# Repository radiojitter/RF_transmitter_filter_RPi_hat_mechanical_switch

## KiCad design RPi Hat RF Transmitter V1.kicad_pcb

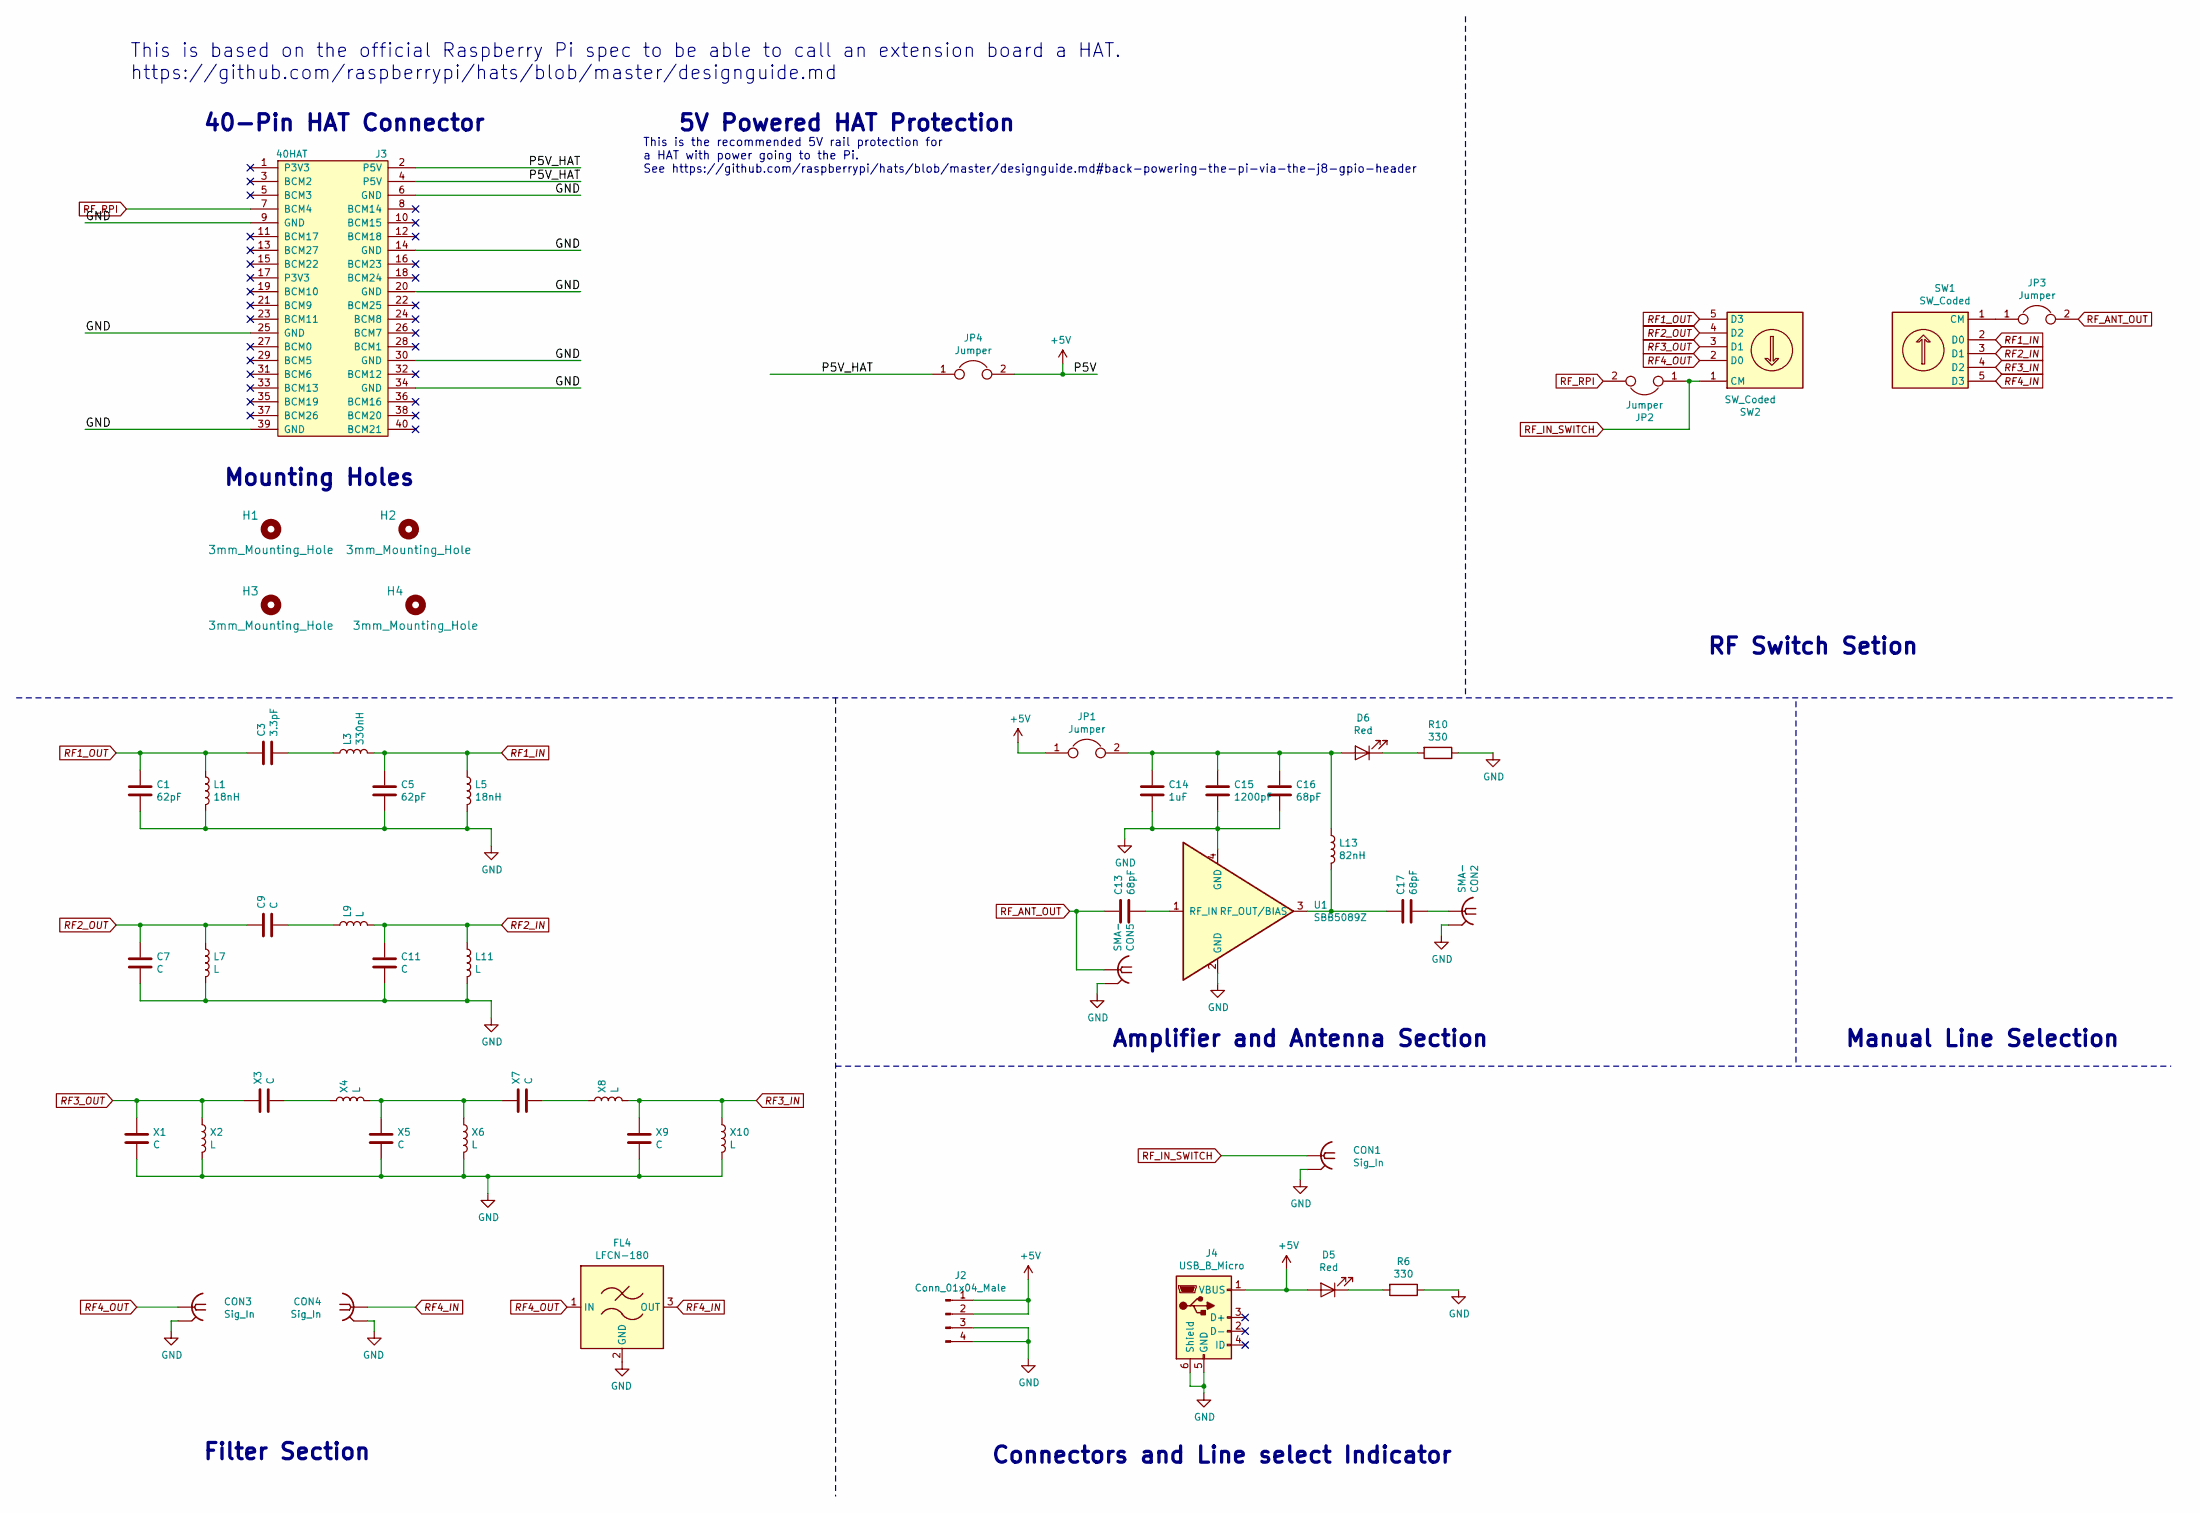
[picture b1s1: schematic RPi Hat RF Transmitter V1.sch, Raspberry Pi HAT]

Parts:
C1, C5: 62pF; C_0805_2012Metric_Pad1.15x1.40mm_HandSolder
C3: 3.3pF; C_0805_2012Metric_Pad1.15x1.40mm_HandSolder
C7, C9, C11: C; C_0805_2012Metric_Pad1.15x1.40mm_HandSolder
C13, C16, C17: 68pF; C_0805_2012Metric_Pad1.15x1.40mm_HandSolder
C14: 1uF; C_0805_2012Metric_Pad1.15x1.40mm_HandSolder
C15: 1200pF; C_0805_2012Metric_Pad1.15x1.40mm_HandSolder
CON1, CON3, CON4: Sig_In; SMA_Amphenol_132291-12_Vertical
CON2, CON5: SMA-; SMA_Amphenol_132291-12_Vertical
D5, D6: Red; LED_0805_2012Metric_Pad1.15x1.40mm_HandSolder
FL4: LFCN-180; Filter_Mini-Circuits_FV1206
H1, H2, H3, H4: 3mm_Mounting_Hole; NPTH_3mm_ID
J2: Conn_01x04_Male; PinHeader_1x04_P2.54mm_Vertical
J3: 40HAT; PinSocket_2x20_P2.54mm_Vertical
J4: USB_B_Micro; USB_Micro-B_Molex-105017-0001
JP1, JP2, JP3, JP4: Jumper; PinHeader_1x02_P2.54mm_Vertical
L1, L5: 18nH; L_0805_2012Metric_Pad1.15x1.40mm_HandSolder
L3: 330nH; L_0805_2012Metric_Pad1.15x1.40mm_HandSolder
L7, L9, L11: L; L_0805_2012Metric_Pad1.15x1.40mm_HandSolder
L13: 82nH; L_0805_2012Metric_Pad1.15x1.40mm_HandSolder
R6, R10: 330; R_0805_2012Metric_Pad1.15x1.40mm_HandSolder
SW1, SW2: SW_Coded; 1x4_switch
U1: SBB5089Z
X1, X3, X5, X7, X9: C; C_0805_2012Metric_Pad1.15x1.40mm_HandSolder
X2, X4, X6, X8, X10: L; L_0805_2012Metric_Pad1.15x1.40mm_HandSolder

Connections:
+5V: D5.2 (A), J2.1, J2.2, J4.1 (VBUS), JP1.1, JP4.2
/P5V_HAT: J3.2 (P5V), J3.4 (P5V), JP4.1
GND: C1.2, C5.2, C7.2, C11.2, C14.2, C15.2, C16.2, CON1.2, CON2.2, CON3.2, CON4.2, CON5.2, FL4.2 (GND), FL4.4 (GND), J2.3, J2.4, J3.6 (GND), J3.9 (GND), J3.14 (GND), J3.20 (GND), J3.25 (GND), J3.30 (GND), J3.34 (GND), J3.39 (GND), J4.5 (GND), J4.6 (Shield), L1.2, L5.2, L7.2, L11.2, R6.1, R10.1, U1.2 (GND), U1.4 (GND), X1.2, X2.2, X5.2, X6.2, X9.2, X10.2
unnamed: C3.2, L3.1
unnamed: C9.2, L9.1
unnamed: C13.2, U1.1 (RF_IN)
unnamed: C14.1, C15.1, C16.1, D6.2 (A), JP1.2, L13.1
unnamed: C17.1, L13.2, U1.3 (RF_OUT/BIAS)
unnamed: C17.2, CON2.1
unnamed: D5.1 (K), R6.2
unnamed: D6.1 (K), R10.2
unnamed: JP3.1, SW1.1 (CM)
unnamed: X3.2, X4.1
unnamed: X4.2, X5.1, X6.1, X7.1
unnamed: X7.2, X8.1
RF1_IN: C5.1, L3.2, L5.1, SW1.2 (D0)
RF1_OUT: C1.1, C3.1, L1.1, SW2.5 (D3)
RF2_IN: C11.1, L9.2, L11.1, SW1.3 (D1)
RF2_OUT: C7.1, C9.1, L7.1, SW2.4 (D2)
RF3_IN: SW1.4 (D2), X8.2, X9.1, X10.1
RF3_OUT: SW2.3 (D1), X1.1, X2.1, X3.1
RF4_IN: CON4.1, FL4.3 (OUT), SW1.5 (D3)
RF4_OUT: CON3.1, FL4.1 (IN), SW2.2 (D0)
RF_ANT_OUT: C13.1, CON5.1, JP3.2
RF_IN_SWITCH: CON1.1, JP2.1, SW2.1 (CM)
RF_RPI: J3.7 (BCM4), JP2.2

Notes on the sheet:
5V Powered HAT Protection
This is the recommended 5V rail protection for a HAT with power going to the Pi. See https://github.com/raspberrypi/hats/blob/master/designguide.md#back-powering-the-pi-via-the-j8-gpio-header
Mounting Holes
40-Pin HAT Connector
This is based on the official Raspberry Pi spec to be able to call an extension board a HAT. https://github.com/raspberrypi/hats/blob/master/designguide.md
Filter Section
RF Switch Setion
Amplifier and Antenna Section
Connectors and Line select Indicator
Manual Line Selection

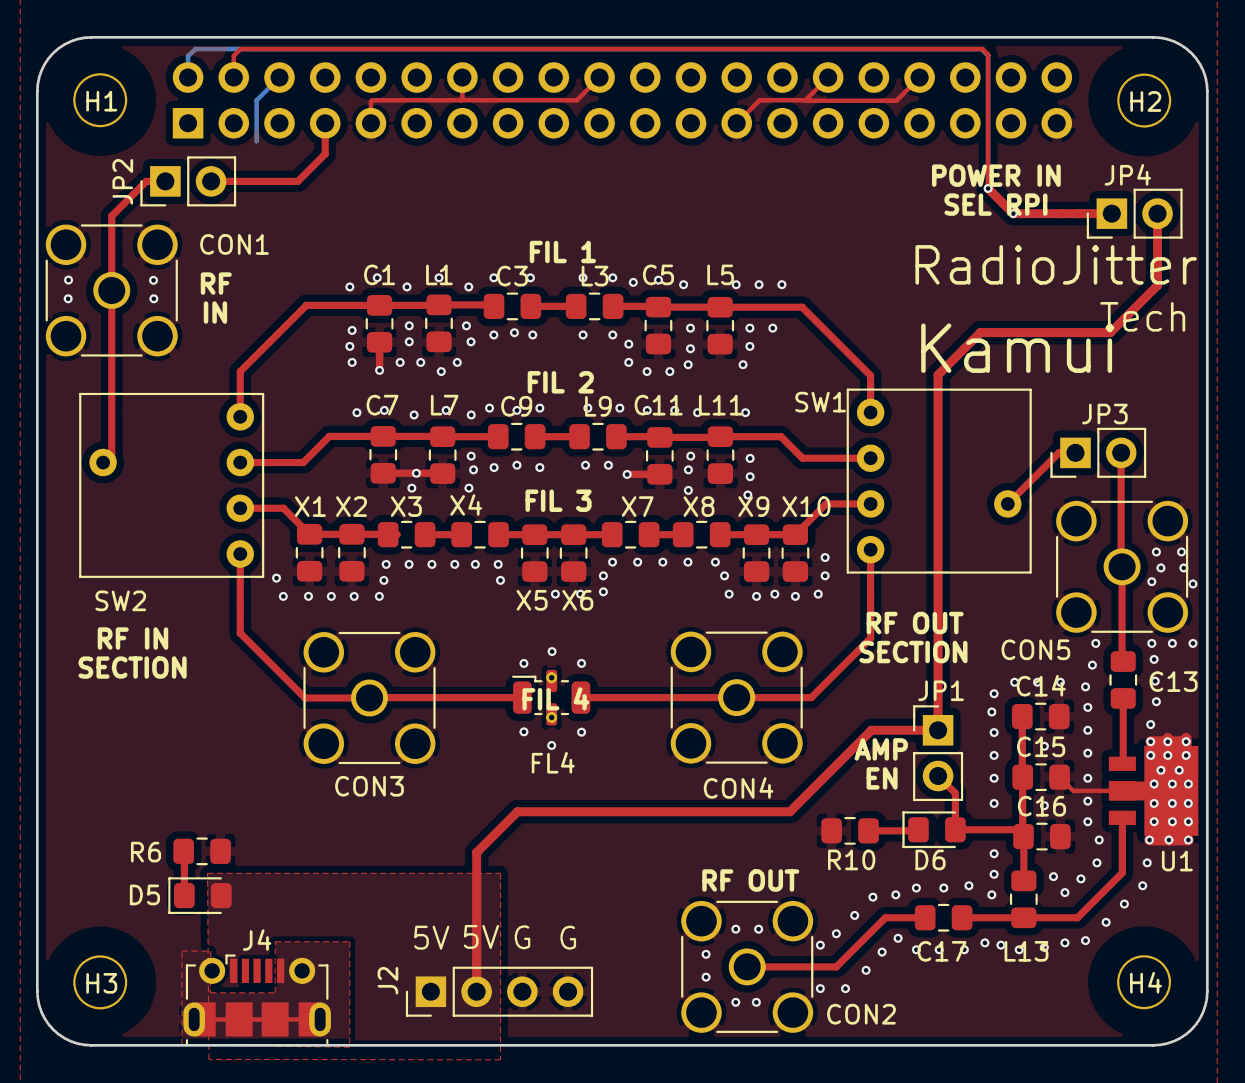
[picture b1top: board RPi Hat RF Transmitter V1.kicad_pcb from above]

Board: 2 copper layers, 65.0 x 56.0 mm, 52 parts (1 on the bottom side), 26 nets.

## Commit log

2019-10-15 Initial commit with digital switch, later commits will remove digital switch
2019-10-15 removes digital switch and puts mechanical switch
2019-10-20 goes on proto production here
